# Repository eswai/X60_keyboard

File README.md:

# X60

TS配列のGH60互換キーボードPCB

- ai03氏のJP60(https://github.com/ai03-2725/JP60)をベースに、配列を変更。
- MITライセンス
- GH60対応の60％ケースで使用可能

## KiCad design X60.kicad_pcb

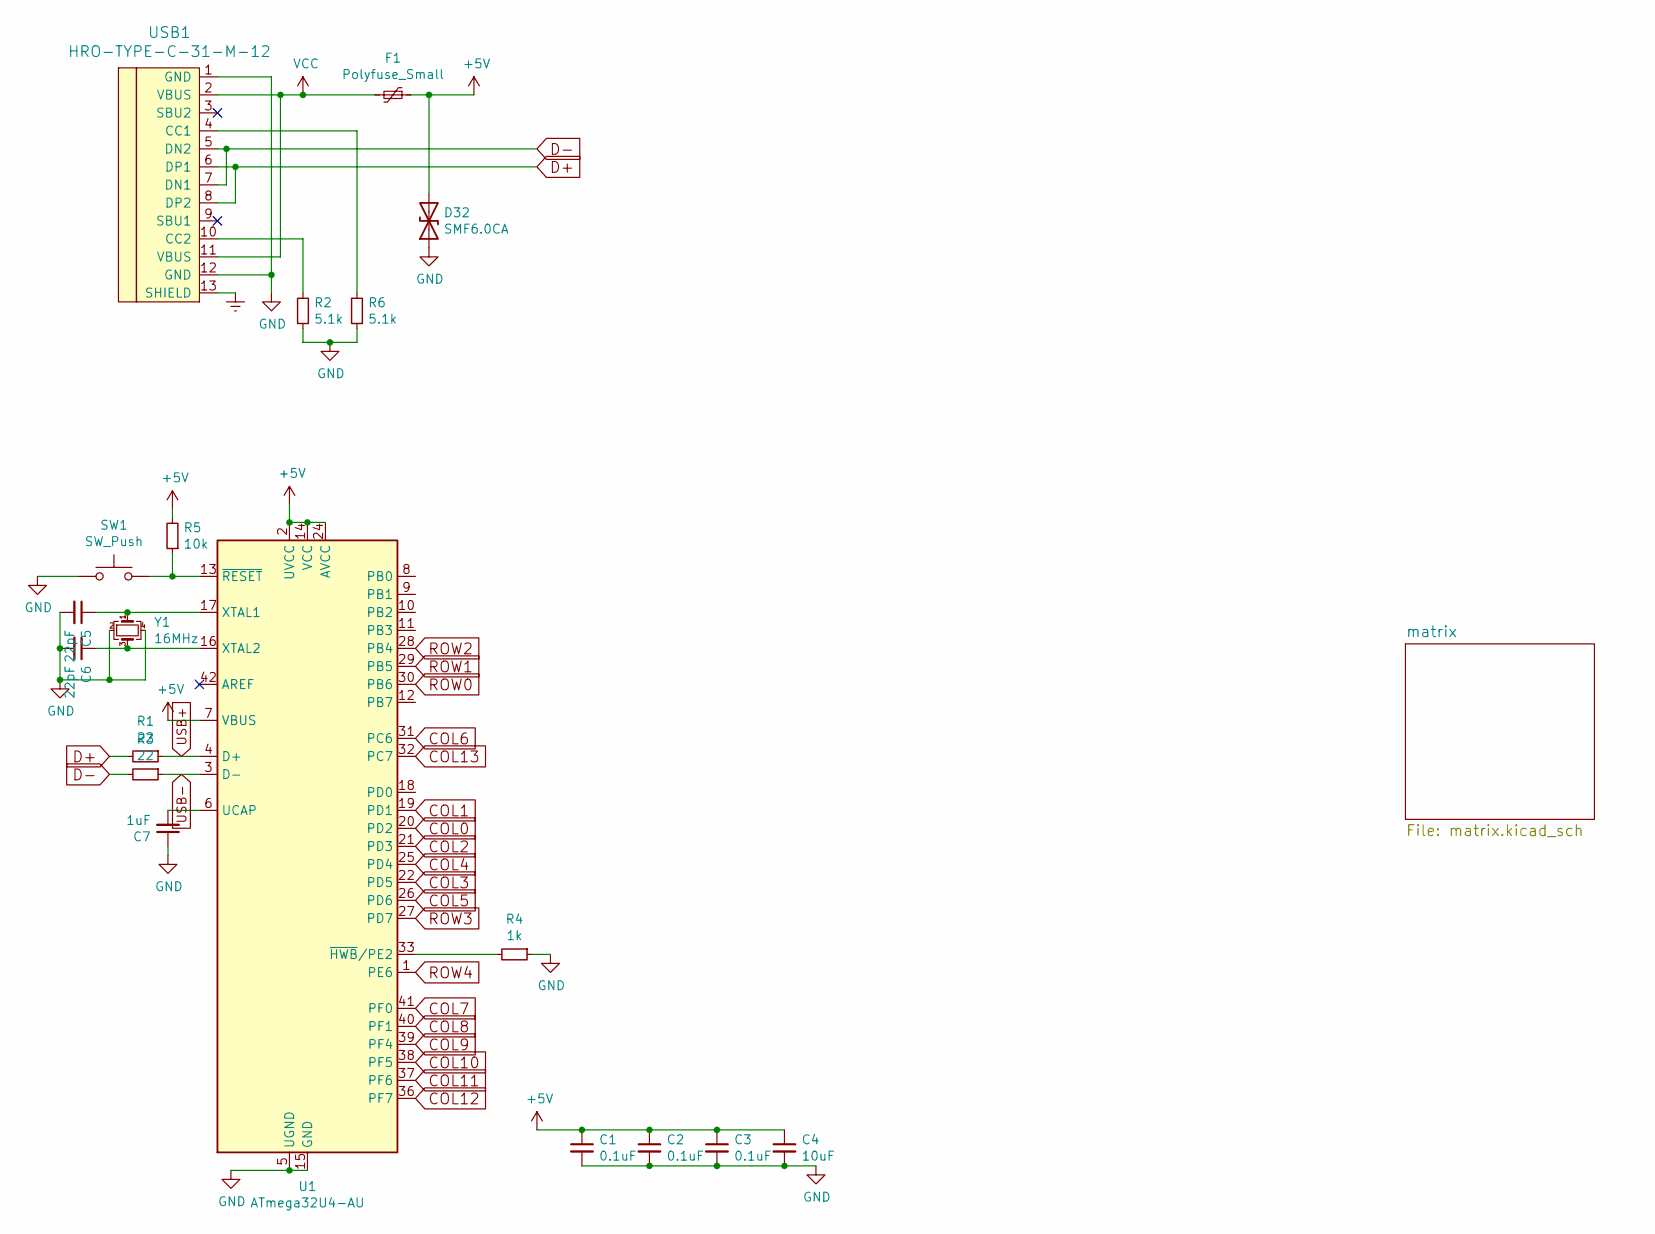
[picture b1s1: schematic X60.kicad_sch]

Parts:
C1, C2, C3: 0.1uF; C_0603_1608Metric_Pad1.08x0.95mm_HandSolder
C4: 10uF; C_0603_1608Metric_Pad1.08x0.95mm_HandSolder
C5, C6: 22pF; C_0603_1608Metric_Pad1.08x0.95mm_HandSolder
C7: 1uF; C_0603_1608Metric_Pad1.08x0.95mm_HandSolder
D32: SMF6.0CA; D_SOD-123
F1: Polyfuse_Small; Fuse_1206_3216Metric
R1, R3: 22; R_0603_1608Metric_Pad0.98x0.95mm_HandSolder
R2, R6: 5.1k; R_0603_1608Metric_Pad0.98x0.95mm_HandSolder
R4: 1k; R_0603_1608Metric_Pad0.98x0.95mm_HandSolder
R5: 10k; R_0603_1608Metric_Pad0.98x0.95mm_HandSolder
SW1: SW_Push; SW_SPST_TL3342
U1: ATmega32U4-AU; TQFP-44_10x10mm_P0.8mm
USB1: HRO-TYPE-C-31-M-12; HRO-TYPE-C-31-M-12-Assembly
Y1: 16MHz; Crystal_SMD_3225-4Pin_3.2x2.5mm

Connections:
+5V: C1.1, C2.1, C3.1, C4.1, D32.2 (A2), F1.1, R5.2, U1.2 (UVCC), U1.7 (VBUS), U1.14 (VCC), U1.24 (AVCC), U1.34 (VCC), U1.44 (AVCC)
COL0: U1.20 (PD2); also elsewhere on the board
COL1: U1.19 (PD1); also elsewhere on the board
COL2: U1.21 (PD3); also elsewhere on the board
COL3: U1.22 (PD5); also elsewhere on the board
COL4: U1.25 (PD4); also elsewhere on the board
COL5: U1.26 (PD6); also elsewhere on the board
COL6: U1.31 (PC6); also elsewhere on the board
COL7: U1.41 (PF0); also elsewhere on the board
COL8: U1.40 (PF1); also elsewhere on the board
COL9: U1.39 (PF4); also elsewhere on the board
COL10: U1.38 (PF5); also elsewhere on the board
COL11: U1.37 (PF6); also elsewhere on the board
COL12: U1.36 (PF7); also elsewhere on the board
COL13: U1.32 (PC7); also elsewhere on the board
D+: R1.2, USB1.6 (DP1), USB1.8 (DP2)
D-: R3.2, USB1.5 (DN2), USB1.7 (DN1)
Earth: USB1.13 (SHIELD)
GND: C1.2, C2.2, C3.2, C4.2, C5.2, C6.2, C7.1, D32.1 (A1), R2.1, R4.1, R6.1, SW1.1, U1.5 (UGND), U1.15 (GND), U1.23 (GND), U1.35 (GND), U1.43 (GND), USB1.1 (GND), USB1.12 (GND), Y1.2, Y1.4
unnamed: C5.1, U1.17 (XTAL1), Y1.1
unnamed: C6.1, U1.16 (XTAL2), Y1.3
unnamed: C7.2, U1.6 (UCAP)
unnamed: R2.2, USB1.10 (CC2)
unnamed: R4.2, U1.33 (~HWB/PE2)
unnamed: R5.1, SW1.2, U1.13 (~RESET)
unnamed: R6.2, USB1.4 (CC1)
ROW0: U1.30 (PB6); also elsewhere on the board
ROW1: U1.29 (PB5); also elsewhere on the board
ROW2: U1.28 (PB4); also elsewhere on the board
ROW3: U1.27 (PD7); also elsewhere on the board
ROW4: U1.1 (PE6); also elsewhere on the board
USB+: R1.1, U1.4 (D+)
USB-: R3.1, U1.3 (D-)
VCC: F1.2, USB1.2 (VBUS), USB1.11 (VBUS)

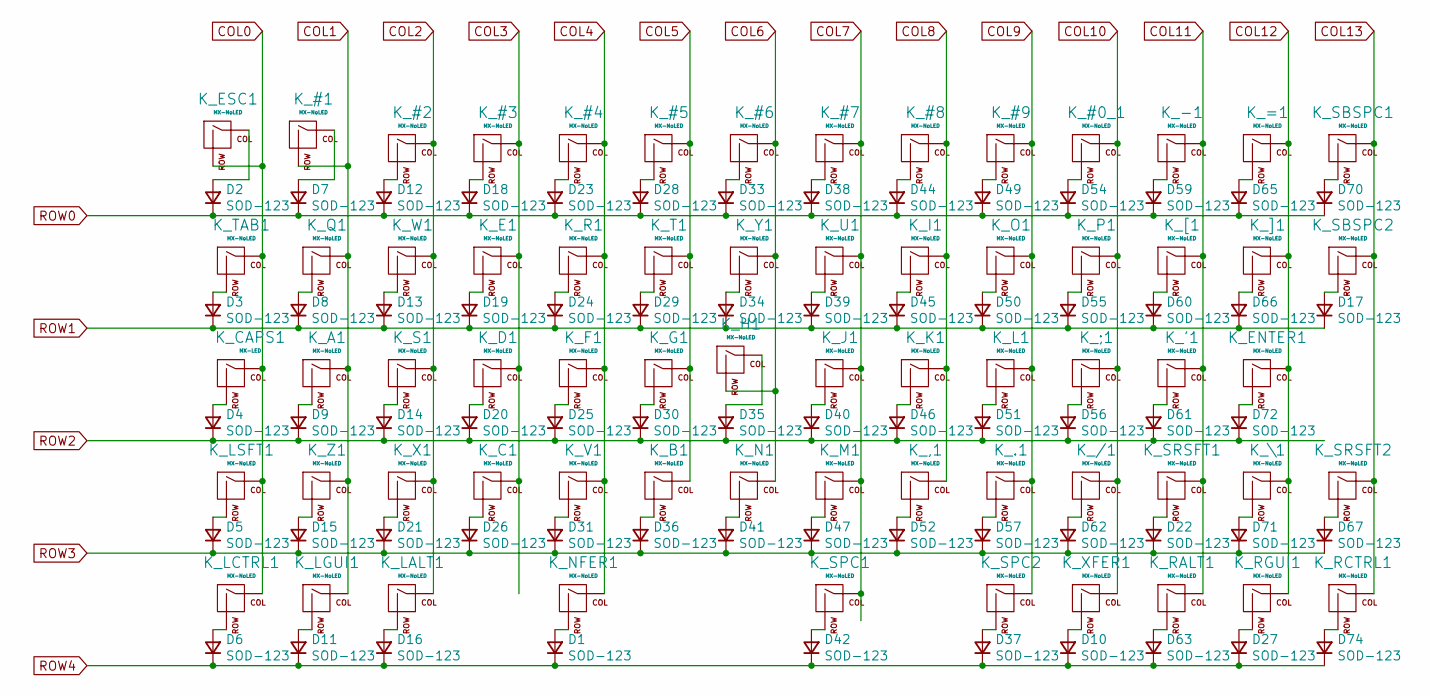
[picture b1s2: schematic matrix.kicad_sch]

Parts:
D1, D2, D3, D4, D5, D6, D7, D8, D9, D10, D11, D12, D13, D14, D15, D16, D17, D18, D19, D20, D21, D22, D23, D24, D25, D26, D27, D28, D29, D30, D31, D33, D34, D35, D36, D37, D38, D39, D40, D41, D42, D44, D45, D46, D47, D49, D50, D51, D52, D54, D55, D56, D57, D59, D60, D61, D62, D63, D65, D66, D67, D70, D71, D72, D74: SOD-123; D_SOD-123
K_#0_1, K_#1, K_#2, K_#3, K_#4, K_#5, K_#6, K_#7, K_#8, K_#9: MX-NoLED; MXOnly-1U-Hotswap
K_'1: MX-NoLED; MXOnly-1U-Hotswap
K_,1: MX-NoLED; MXOnly-1U-Hotswap
K_-1: MX-NoLED; MXOnly-1U-Hotswap
K_.1: MX-NoLED; MXOnly-1U-Hotswap
K_/1: MX-NoLED; MXOnly-1U-Hotswap
K_;1: MX-NoLED; MXOnly-1U-Hotswap
K_=1: MX-NoLED; MXOnly-1U-Hotswap
K_A1: MX-NoLED; MXOnly-1U-Hotswap
K_B1: MX-NoLED; MXOnly-1U-Hotswap
K_C1: MX-NoLED; MXOnly-1U-Hotswap
K_CAPS1: MX-LED; MXOnly-1.75U-Hotswap
K_D1: MX-NoLED; MXOnly-1U-Hotswap
K_E1: MX-NoLED; MXOnly-1U-Hotswap
K_ENTER1: MX-NoLED; MXOnly-2.25U-Hotswap-ReversedStabilizers
K_ESC1: MX-NoLED; MXOnly-1U-Hotswap
K_F1: MX-NoLED; MXOnly-1U-Hotswap
K_G1: MX-NoLED; MXOnly-1U-Hotswap
K_H1: MX-NoLED; MXOnly-1U-Hotswap
K_I1: MX-NoLED; MXOnly-1U-Hotswap
K_J1: MX-NoLED; MXOnly-1U-Hotswap
K_K1: MX-NoLED; MXOnly-1U-Hotswap
K_L1: MX-NoLED; MXOnly-1U-Hotswap
K_LALT1: MX-NoLED; MXOnly-1.5U-Hotswap
K_LCTRL1: MX-NoLED; MXOnly-1.25U-Hotswap
K_LGUI1: MX-NoLED; MXOnly-1.5U-Hotswap
K_LSFT1: MX-NoLED; MXOnly-1.5U-Hotswap
K_M1: MX-NoLED; MXOnly-1U-Hotswap
K_N1: MX-NoLED; MXOnly-1U-Hotswap
K_NFER1: MX-NoLED; MXOnly-2.75U-Hotswap-ReversedStabilizers
K_O1: MX-NoLED; MXOnly-1U-Hotswap
K_P1: MX-NoLED; MXOnly-1U-Hotswap
K_Q1: MX-NoLED; MXOnly-1U-Hotswap
K_R1: MX-NoLED; MXOnly-1U-Hotswap
K_RALT1: MX-NoLED; MXOnly-1U-Hotswap
K_RCTRL1: MX-NoLED; MXOnly-1U-Hotswap
K_RGUI1: MX-NoLED; MXOnly-1U-Hotswap
K_S1: MX-NoLED; MXOnly-1U-Hotswap
K_SBSPC1, K_SBSPC2: MX-NoLED; MXOnly-1U-Hotswap
K_SPC1: MX-NoLED; MXOnly-2.25U-Hotswap-ReversedStabilizers
K_SPC2: MX-NoLED; MXOnly-1.5U-Hotswap
K_SRSFT1, K_SRSFT2: MX-NoLED; MXOnly-1U-Hotswap
K_T1: MX-NoLED; MXOnly-1U-Hotswap
K_TAB1: MX-NoLED; MXOnly-1.5U-Hotswap
K_U1: MX-NoLED; MXOnly-1U-Hotswap
K_V1: MX-NoLED; MXOnly-1U-Hotswap
K_W1: MX-NoLED; MXOnly-1U-Hotswap
K_X1: MX-NoLED; MXOnly-1U-Hotswap
K_XFER1: MX-NoLED; MXOnly-1.25U-Hotswap
K_Y1: MX-NoLED; MXOnly-1U-Hotswap
K_Z1: MX-NoLED; MXOnly-1U-Hotswap
K_[1: MX-NoLED; MXOnly-1U-Hotswap
K_\1: MX-NoLED; MXOnly-1U-Hotswap
K_]1: MX-NoLED; MXOnly-1.5U-Hotswap

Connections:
COL0: K_CAPS1.1 (COL), K_ESC1.2 (ROW), K_LCTRL1.1 (COL), K_LSFT1.1 (COL), K_TAB1.1 (COL); also elsewhere on the board
COL1: K_#1.2 (ROW), K_A1.1 (COL), K_LGUI1.1 (COL), K_Q1.1 (COL), K_Z1.1 (COL); also elsewhere on the board
COL2: K_#2.1 (COL), K_LALT1.1 (COL), K_S1.1 (COL), K_W1.1 (COL), K_X1.1 (COL); also elsewhere on the board
COL3: K_#3.1 (COL), K_C1.1 (COL), K_D1.1 (COL), K_E1.1 (COL); also elsewhere on the board
COL4: K_#4.1 (COL), K_F1.1 (COL), K_NFER1.1 (COL), K_R1.1 (COL), K_V1.1 (COL); also elsewhere on the board
COL5: K_#5.1 (COL), K_B1.1 (COL), K_G1.1 (COL), K_T1.1 (COL); also elsewhere on the board
COL6: K_#6.1 (COL), K_H1.2 (ROW), K_N1.1 (COL), K_Y1.1 (COL); also elsewhere on the board
COL7: K_#7.1 (COL), K_J1.1 (COL), K_M1.1 (COL), K_SPC1.1 (COL), K_U1.1 (COL); also elsewhere on the board
COL8: K_#8.1 (COL), K_,1.1 (COL), K_I1.1 (COL), K_K1.1 (COL); also elsewhere on the board
COL9: K_#9.1 (COL), K_.1.1 (COL), K_L1.1 (COL), K_O1.1 (COL), K_SPC2.1 (COL); also elsewhere on the board
COL10: K_#0_1.1 (COL), K_/1.1 (COL), K_;1.1 (COL), K_P1.1 (COL), K_XFER1.1 (COL); also elsewhere on the board
COL11: K_'1.1 (COL), K_-1.1 (COL), K_RALT1.1 (COL), K_SRSFT1.1 (COL), K_[1.1 (COL); also elsewhere on the board
COL12: K_=1.1 (COL), K_ENTER1.1 (COL), K_RGUI1.1 (COL), K_\1.1 (COL), K_]1.1 (COL); also elsewhere on the board
COL13: K_RCTRL1.1 (COL), K_SBSPC1.1 (COL), K_SBSPC2.1 (COL), K_SRSFT2.1 (COL); also elsewhere on the board
unnamed: D1.2 (A), K_NFER1.2 (ROW)
unnamed: D2.2 (A), K_ESC1.1 (COL)
unnamed: D3.2 (A), K_TAB1.2 (ROW)
unnamed: D4.2 (A), K_CAPS1.2 (ROW)
unnamed: D5.2 (A), K_LSFT1.2 (ROW)
unnamed: D6.2 (A), K_LCTRL1.2 (ROW)
unnamed: D7.2 (A), K_#1.1 (COL)
unnamed: D8.2 (A), K_Q1.2 (ROW)
unnamed: D9.2 (A), K_A1.2 (ROW)
unnamed: D10.2 (A), K_XFER1.2 (ROW)
unnamed: D11.2 (A), K_LGUI1.2 (ROW)
unnamed: D12.2 (A), K_#2.2 (ROW)
unnamed: D13.2 (A), K_W1.2 (ROW)
unnamed: D14.2 (A), K_S1.2 (ROW)
unnamed: D15.2 (A), K_Z1.2 (ROW)
unnamed: D16.2 (A), K_LALT1.2 (ROW)
unnamed: D17.2 (A), K_SBSPC2.2 (ROW)
unnamed: D18.2 (A), K_#3.2 (ROW)
unnamed: D19.2 (A), K_E1.2 (ROW)
unnamed: D20.2 (A), K_D1.2 (ROW)
unnamed: D21.2 (A), K_X1.2 (ROW)
unnamed: D22.2 (A), K_SRSFT1.2 (ROW)
unnamed: D23.2 (A), K_#4.2 (ROW)
unnamed: D24.2 (A), K_R1.2 (ROW)
unnamed: D25.2 (A), K_F1.2 (ROW)
unnamed: D26.2 (A), K_C1.2 (ROW)
unnamed: D27.2 (A), K_RGUI1.2 (ROW)
unnamed: D28.2 (A), K_#5.2 (ROW)
unnamed: D29.2 (A), K_T1.2 (ROW)
unnamed: D30.2 (A), K_G1.2 (ROW)
unnamed: D31.2 (A), K_V1.2 (ROW)
unnamed: D33.2 (A), K_#6.2 (ROW)
unnamed: D34.2 (A), K_Y1.2 (ROW)
unnamed: D35.2 (A), K_H1.1 (COL)
unnamed: D36.2 (A), K_B1.2 (ROW)
unnamed: D37.2 (A), K_SPC2.2 (ROW)
unnamed: D38.2 (A), K_#7.2 (ROW)
unnamed: D39.2 (A), K_U1.2 (ROW)
unnamed: D40.2 (A), K_J1.2 (ROW)
unnamed: D41.2 (A), K_N1.2 (ROW)
unnamed: D42.2 (A), K_SPC1.2 (ROW)
unnamed: D44.2 (A), K_#8.2 (ROW)
unnamed: D45.2 (A), K_I1.2 (ROW)
unnamed: D46.2 (A), K_K1.2 (ROW)
unnamed: D47.2 (A), K_M1.2 (ROW)
unnamed: D49.2 (A), K_#9.2 (ROW)
unnamed: D50.2 (A), K_O1.2 (ROW)
unnamed: D51.2 (A), K_L1.2 (ROW)
unnamed: D52.2 (A), K_,1.2 (ROW)
unnamed: D54.2 (A), K_#0_1.2 (ROW)
unnamed: D55.2 (A), K_P1.2 (ROW)
unnamed: D56.2 (A), K_;1.2 (ROW)
unnamed: D57.2 (A), K_.1.2 (ROW)
unnamed: D59.2 (A), K_-1.2 (ROW)
unnamed: D60.2 (A), K_[1.2 (ROW)
unnamed: D61.2 (A), K_'1.2 (ROW)
unnamed: D62.2 (A), K_/1.2 (ROW)
unnamed: D63.2 (A), K_RALT1.2 (ROW)
unnamed: D65.2 (A), K_=1.2 (ROW)
unnamed: D66.2 (A), K_]1.2 (ROW)
unnamed: D67.2 (A), K_SRSFT2.2 (ROW)
unnamed: D70.2 (A), K_SBSPC1.2 (ROW)
unnamed: D71.2 (A), K_\1.2 (ROW)
unnamed: D72.2 (A), K_ENTER1.2 (ROW)
unnamed: D74.2 (A), K_RCTRL1.2 (ROW)
ROW0: D2.1 (K), D7.1 (K), D12.1 (K), D18.1 (K), D23.1 (K), D28.1 (K), D33.1 (K), D38.1 (K), D44.1 (K), D49.1 (K), D54.1 (K), D59.1 (K), D65.1 (K), D70.1 (K); also elsewhere on the board
ROW1: D3.1 (K), D8.1 (K), D13.1 (K), D17.1 (K), D19.1 (K), D24.1 (K), D29.1 (K), D34.1 (K), D39.1 (K), D45.1 (K), D50.1 (K), D55.1 (K), D60.1 (K), D66.1 (K); also elsewhere on the board
ROW2: D4.1 (K), D9.1 (K), D14.1 (K), D20.1 (K), D25.1 (K), D30.1 (K), D35.1 (K), D40.1 (K), D46.1 (K), D51.1 (K), D56.1 (K), D61.1 (K), D72.1 (K); also elsewhere on the board
ROW3: D5.1 (K), D15.1 (K), D21.1 (K), D22.1 (K), D26.1 (K), D31.1 (K), D36.1 (K), D41.1 (K), D47.1 (K), D52.1 (K), D57.1 (K), D62.1 (K), D67.1 (K), D71.1 (K); also elsewhere on the board
ROW4: D1.1 (K), D6.1 (K), D10.1 (K), D11.1 (K), D16.1 (K), D27.1 (K), D37.1 (K), D42.1 (K), D63.1 (K), D74.1 (K); also elsewhere on the board

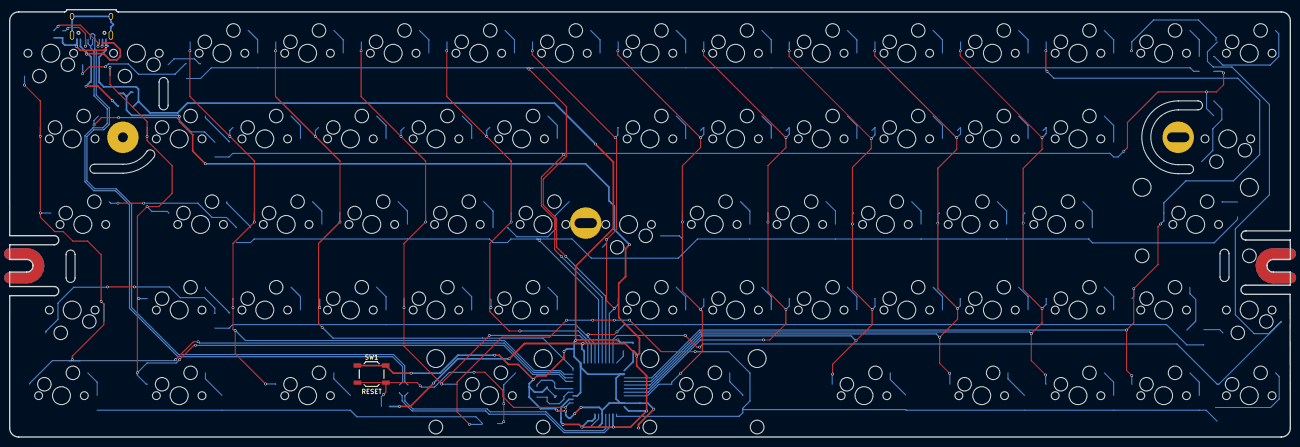
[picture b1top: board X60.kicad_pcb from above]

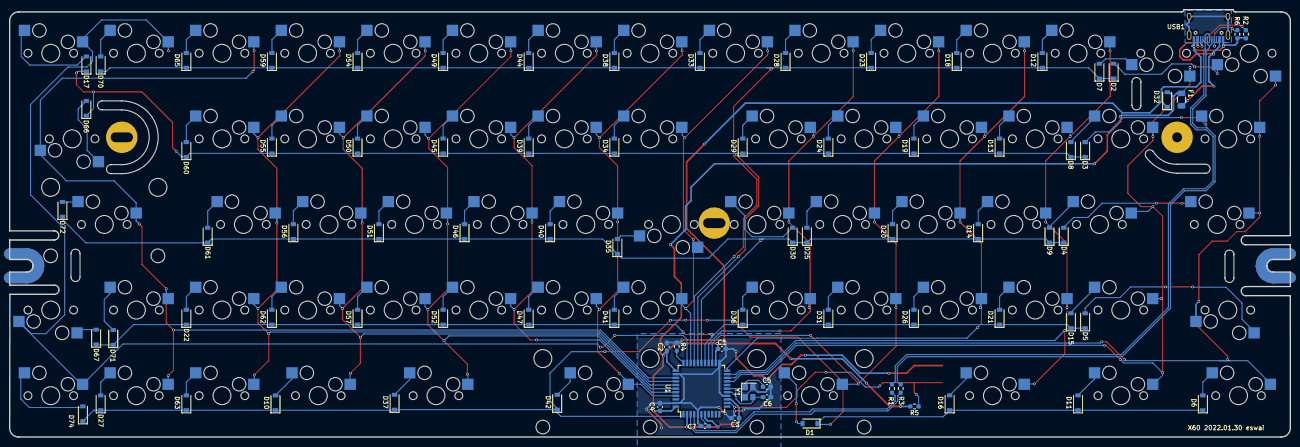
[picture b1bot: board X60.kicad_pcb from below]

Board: 2 copper layers, 285.0 x 95.1 mm, 149 parts (83 on the bottom side), 98 nets.

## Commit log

2023-03-01 README
2023-03-01 キーレイアウト
